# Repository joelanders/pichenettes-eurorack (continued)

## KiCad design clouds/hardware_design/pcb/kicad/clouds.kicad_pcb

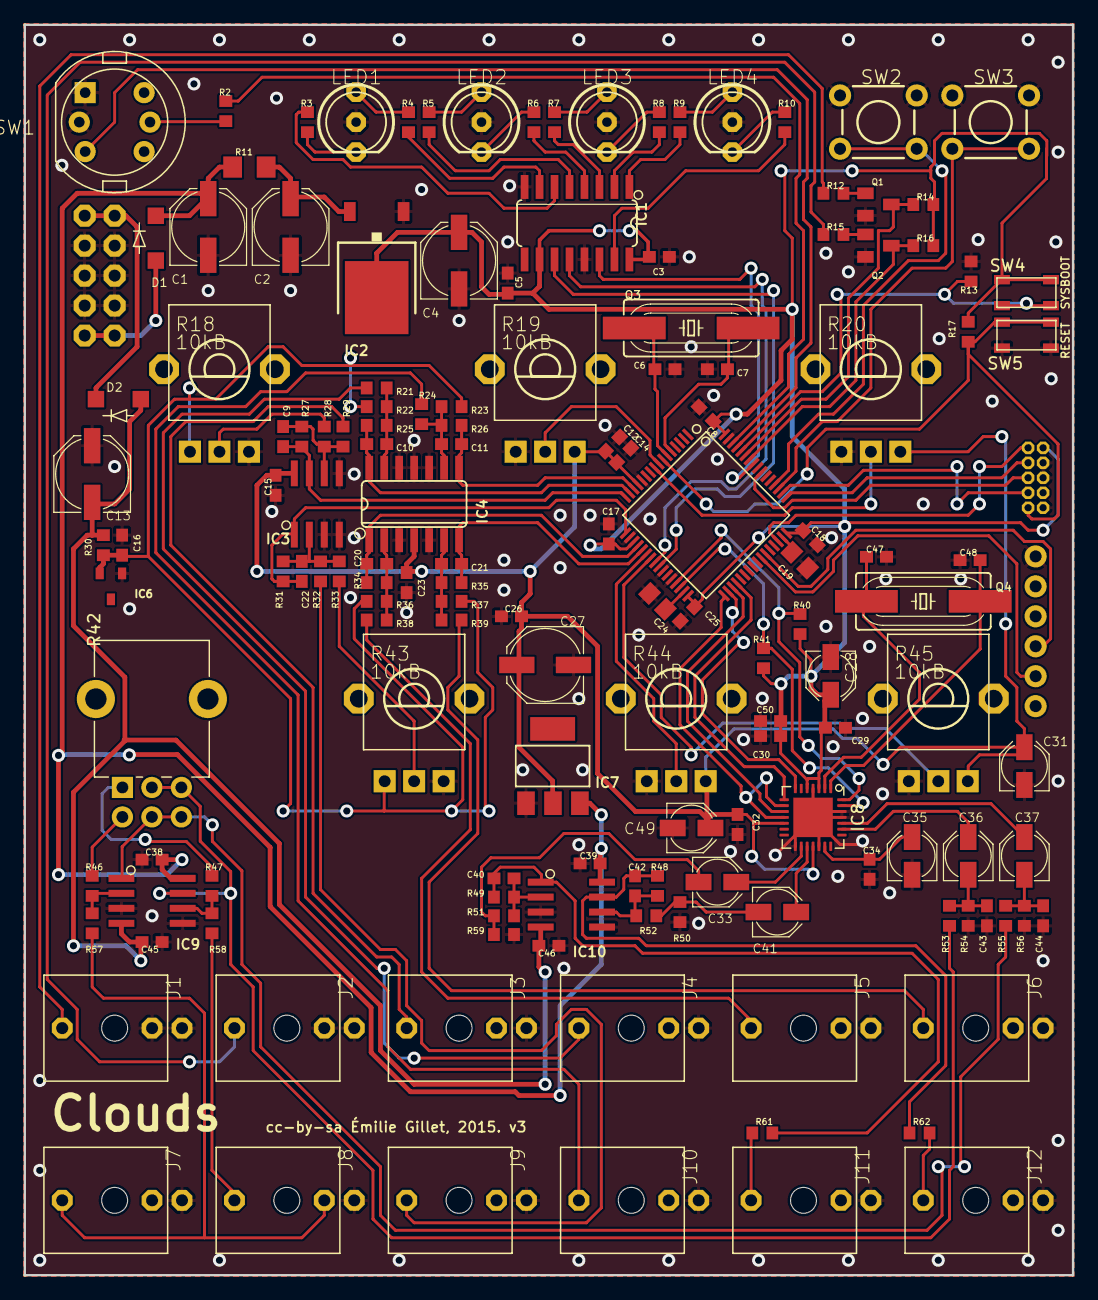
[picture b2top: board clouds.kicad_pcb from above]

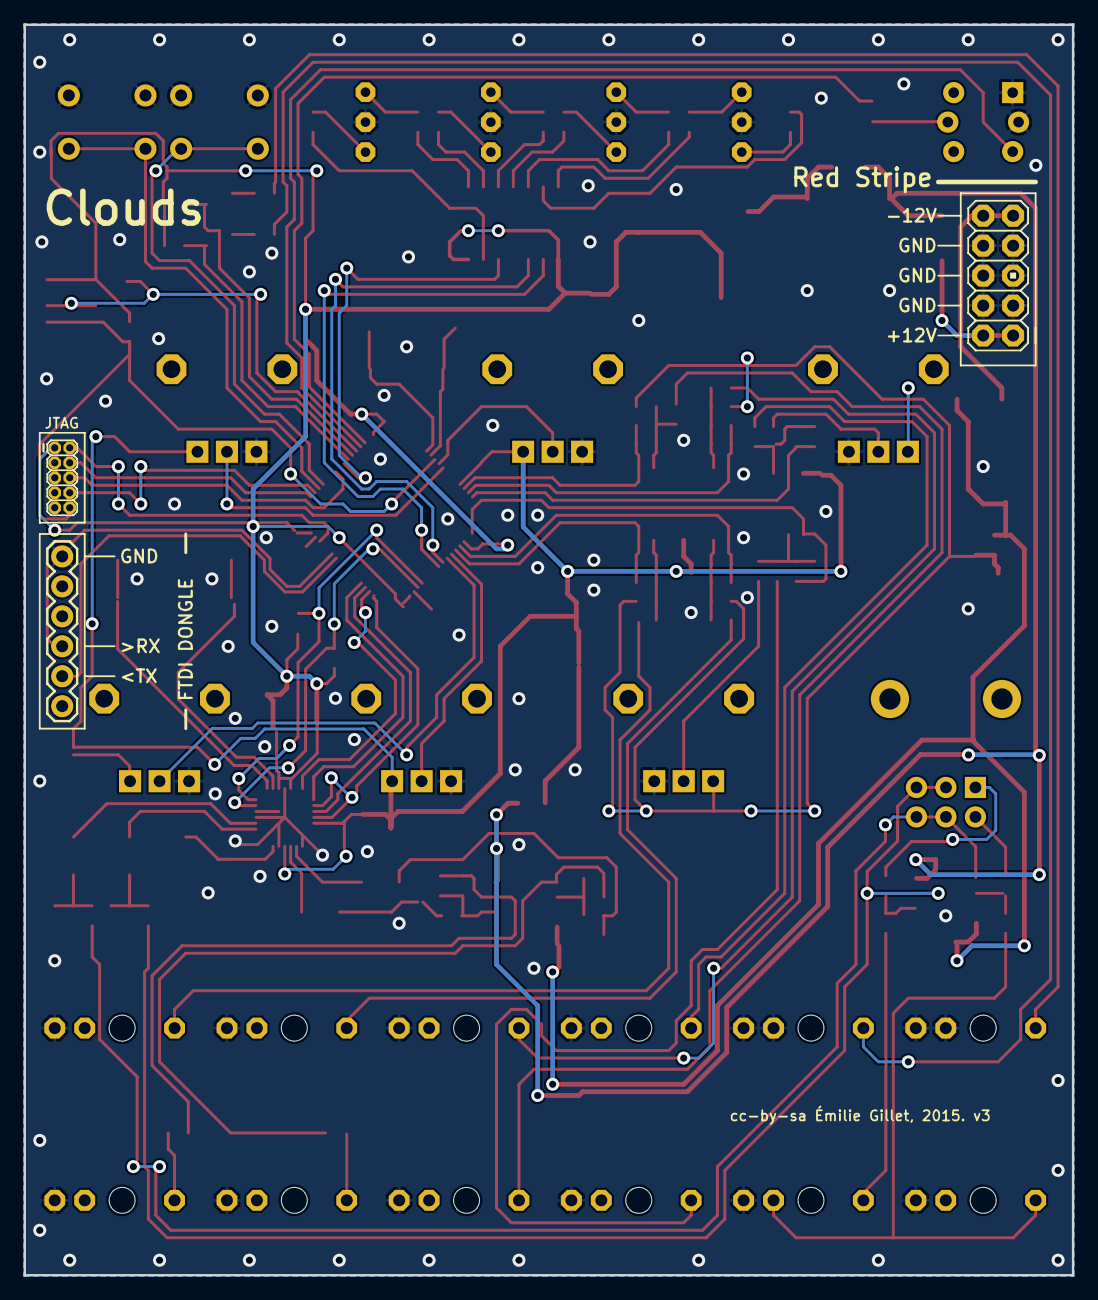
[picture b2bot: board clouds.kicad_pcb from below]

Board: 2 copper layers, 88.9 x 106.0 mm, 150 parts (3 on the bottom side), 106 nets.

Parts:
C1, C2, C4, C13, C27: 47u; PANASONIC_D
C3, C5, C8, C14, C15, C16, C17, C18, C23, C25, C26, C29, C30, C32, C34, C38, C39, C45, C46: 100n; C0603
C6, C7, C40, C42, C47, C48: 18p; C0603
C9, C10, C11, C20, C21, C22: 1n; C0603
C12, C50: 1u; C0603
C19, C24: 2.2u; C0805
C28, C31, C33, C35, C36, C37, C41, C49: 10u; PANASONIC_B
C43, C44: 220p; C0603
D1, D2: 1N5819HW; SOD123
IC1: 74595D; SO16
IC2: LM1117-3.3; TO252
IC3: MCP6002; SO08
IC4: MCP6004; SO14
IC5: STM32F405RGT6; TQFP-10X10-64
IC6: LM4040B10; DBZ_R-PDSO-G3
IC7: LM1117-3.3; SOT223
IC8: WM8731; QFN-28-1EP_5x5mm_P0.5mm_EP3.35x3.35mm
IC9, IC10: TL072D; SO08
J1, J2, J3, J4, J5, J6, J7, J8, J9, J10, J11, J12: PJ301_THONKICONN6; WQP_PJ_301M6
JP1: M06SIP; 1X06
JP2: M05X2MINIJTAG; 2X5-1.27
JP3: M05X2PTH; AVR_ICSP
LED1, LED2, LED3, LED4: WP59EGW; LED-BICOLOR-THROUGHHOLE-5MM
Q1, Q2: MMBT3904; SOT23-BEC
Q3: 8MHz; HC49UP
Q4: 12.288MHz; HC49UP
R2: 1k; R0603
R3, R4, R5, R6, R7, R8, R9, R10: 68; R0603
R11: 4.7; R1206
R12, R15, R21, R24, R29, R32, R38, R39: 100k; R0603
R13, R14, R16, R17: 10k; R0603
R18, R19, R20, R43, R44, R45: 10kB; ALPS_POT_VERTICAL_PS
R22, R23, R28, R33, R37: 200k; R0603
R25, R26, R35: 33k; R0603
R27, R31: 66.5k; R0603
R30: 470; R0603
R34: 47k; R0603
R36: 180k; R0603
R40, R41: 2.2k; R0603
R42: R_Potentiometer_Dual_Separate; Potentiometer_Alpha_RD902F-40-00D_Dual_Vertical_CircularHol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
R46, R47: 3.3k; R0603
R48, R49, R50, R59: 39k; R0603
R51, R52, R53, R54, R55, R56: 5.6k; R0603
R57, R58: 22k; R0603
R61, R62: 1.0k; R0603
SW1: SW_Push_LED; C&K_D6R
SW2, SW3: TAC_SWITCHPTH; TACTILE-PTH
SW4, SW5: EVQQ2; k2-1808 pushbutton switch

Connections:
+3V3: C3.1, C4.+, C5.1, C8.1, C17.1, C18.1, C25.1, C28.+, C29.1, C30.1, C50.1, IC1.10 (SCL), IC1.16 (VCC), IC2.3 (VOUT), IC5.19 (VDD_4), IC5.32 (VDD_1), IC5.48 (VDD_2), IC5.64 (VDD_3), IC8.3 (DCVDD), IC8.5 (DBVDD), JP2.1, R14.2, R16.2, R17.2, R40.2, R41.2, SW4.B (S), SW4.B' (S1)
+3V3_A: C12.1, C14.1, C15.1, C23.1, C26.1, C27.+, C31.+, C32.1, C49.+, IC3.8 (V+), IC4.4 (V+), IC5.13 (VDDA), IC7.2 (VOUT), IC8.12 (HPVDD), IC8.18 (AVDD), R19.P$1 (E), R20.P$1 (E), R44.P$1 (E), R45.P$1 (E)
/clouds_2/BOOT_FLASH: IC5.60 (BOOT0), R13.2, SW4.A, SW4.A' (P1)
/clouds_2/I2C_SCL: IC5.29 (PB10/SPI2_SCK/I2S_SCK/I2C2_SCL/USART3_TX), IC8.28 (SCLK), R40.1
/clouds_2/I2C_SDA: IC5.30 (PB11/I2C2_SDA/USART3_RX), IC8.27 (SDIN), R41.1
/clouds_2/I2S_LRCK: IC5.33 (PB12/SPI2_NSS/I2S2_WS/I2C2_SMBA/USART3_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), IC8.9 (DACLRC), IC8.11 (ADCLRC)
/clouds_2/I2S_SCK: IC5.34 (PB13/SPI2_SCK/I2S2_SCK/USART3_CTS/TIM1_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), IC8.7 (BCLK)
/clouds_2/I2S_SIN: IC5.35 (PB14/SPI2_MISO/USART3_RTS/TIM1_CH2N), IC8.10 (ADCDAT)
/clouds_2/I2S_SOUT: IC5.36 (PB15/SPI2_MOSI/I2S2_SD/TIM1_CH3N), IC8.8 (DACDAT)
/clouds_2/JTCK: IC5.49 (PA14/JTCK-SWCLK), JP2.4
/clouds_2/JTDI: IC5.50 (PA15/JTDI/SPI3_NSS/I2S3_WS), JP2.8
/clouds_2/JTDO: IC5.55 (PB3/JTDO/SPI3_SCK/I2S3_SCK), JP2.6
/clouds_2/JTMS: IC5.46 (PA13/JTMS-SWDAT), JP2.2
/clouds_2/RESET: IC5.7 (NRST), JP2.10, R17.1, SW5.B (S), SW5.B' (S1)
/clouds_2/RX: IC5.43 (PA10/USART1_RX/TIM1_CH3), JP1.4
/clouds_2/TX: IC5.42 (PA9/USART1_TX/TIM1_CH2), JP1.5
AREF_-10: C16.1, IC6.2 (A), R18.P$3 (A), R22.2, R23.2, R30.2, R36.2, R37.2, R43.P$3 (A)
BLEND_CV: C21.2, IC4.7 (OUT), IC5.21 (PA5/SPI1_SCK/ADC5/DAC2), R35.1
BLEND_POT: IC5.23 (PA7/SPI1_MOSI/ADC7/TIM3_CH2), R45.P$2 (S)
DENSITY_CV: C22.2, IC3.1 (OUT), IC5.17 (PA3/USART2_RX/ADC3/TIM2_CH4), R31.1
GND: C1.-, C2.-, C3.2, C4.-, C5.2, C6.1, C7.1, C8.2, C12.2, C13.+, C14.2, C15.2, C16.2, C17.2, C18.2, C19.2, C23.2, C24.2, C25.2, C26.2, C27.-, C28.-, C29.2, C30.2, C31.-, C32.2, C34.2, C35.-, C38.2, C39.2, C43.2, C44.2, C45.1, C46.1, C47.1, C48.1, C49.-, C50.2, IC1.8 (GND), IC1.13 (G), IC2.1 (GND), IC3.3 (+IN), IC3.4 (V-), IC3.5 (+IN), IC4.3 (+IN), IC4.5 (+IN), IC4.10 (+IN), IC4.11 (V-), IC4.12 (+IN), IC5.12 (VSSA), IC5.18 (VSS_4), IC5.26 (PB0/ADC8/TIM3_CH3), IC5.28 (PB2/BOOT1), IC5.63 (VSS_3), IC6.1 (C), IC7.1 (GND), IC8.4 (DGND), IC8.15 (HPGND), IC8.19 (AGND), IC8.25 (MODE), IC8.26 (CSB), IC8.29 (PAD), IC9.3 (+IN), IC9.5 (+IN), IC10.3 (+IN), IC10.5 (+IN), J1.P1 (1), J1.P2 (2), J2.P1 (1), J2.P2 (2), J3.P1 (1), J4.P1 (1), J5.P1 (1), J6.P1 (1), J7.P1 (1), J8.P1 (1), J9.P1 (1), J10.P1 (1), J11.P1 (1), J12.P1 (1), JP1.1, JP2.3, JP2.5, JP2.9, JP3.3, JP3.4, JP3.5, JP3.6, JP3.7, JP3.8, LED1.2 (C), LED2.2 (C), LED3.2 (C), LED4.2 (C), Q1.E, Q2.E, R13.1, R18.P$1 (E), R19.P$3 (A), R20.P$3 (A), R43.P$1 (E), R44.P$3 (A), R45.P$3 (A), R50.1, R54.1, R56.1, R59.1, SW1.1, SW1.2, SW2.1, SW2.2, SW3.1, SW3.2, SW5.A, SW5.A' (P1)
LED_DATA: IC1.14 (SER), IC5.57 (PB5/I2C1_SMBA/SPI1_MOSI/SPI3_MOSI/I2S3_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)
LED_EN: IC1.12 (RCK), IC5.24 (PC4/ADC14)
LED_REC: IC5.62 (PB9/SPI2_NSS/I2S2_WS/I2C1_SDA/TIM4_CH4), R2.1
LED_SCK: IC1.11 (SCK), IC5.25 (PC5/ADC15)
LIN: C37.+, IC8.24 (LLINEIN)
LOUT: C33.+, IC8.16 (LOUT)
unnamed: C2.+, IC2.2 (VIN), R11.2
unnamed: C6.2, IC5.6 (PD1/OSC_OUT), Q3.1
unnamed: C7.2, IC5.5 (PD0/OSC_IN), Q3.2
unnamed: C9.1, IC3.6 (-IN), R27.2, R28.1, R29.1
unnamed: C10.1, IC4.13 (-IN), R21.1, R22.1, R25.2
unnamed: C11.1, IC4.9 (-IN), R23.1, R24.1, R26.2
unnamed: C19.1, IC5.47 (VCAP_2)
unnamed: C20.1, IC4.2 (-IN), R34.2, R36.1, R38.1
unnamed: C21.1, IC4.6 (-IN), R35.2, R37.1, R39.1
unnamed: C22.1, IC3.2 (-IN), R31.2, R32.1, R33.1
unnamed: C24.1, IC5.31 (VCAP_1)
unnamed: C33.-, R51.2, R59.2
unnamed: C34.1, C35.+, IC8.20 (VMID)
unnamed: C36.-, C43.1, R53.1, R54.2
unnamed: C37.-, C44.1, R55.1, R56.2
unnamed: C40.1, IC10.2 (-IN), R49.2, R51.1
unnamed: C40.2, IC10.1 (OUT), R49.1, R61.2
unnamed: C41.-, R50.2, R52.2
unnamed: C42.1, IC10.6 (-IN), R48.2, R52.1
unnamed: C42.2, IC10.7 (OUT), R48.1, R62.2
unnamed: C47.2, IC8.2 (XTO), Q4.1
unnamed: C48.2, IC8.1 (XTI/MCLK), Q4.2
unnamed: D1.A, JP3.1, JP3.2
unnamed: D2.C, JP3.9, JP3.10
unnamed: IC1.1 (QB), R9.2
unnamed: IC1.2 (QC), R8.2
unnamed: IC1.3 (QD), R7.2
unnamed: IC1.4 (QE), R6.2
unnamed: IC1.5 (QF), R5.2
unnamed: IC1.6 (QG), R3.2
unnamed: IC1.7 (QH), R4.2
unnamed: IC1.15 (QA), R10.2
unnamed: IC9.1 (OUT), R42.5, R42.6, R55.2
unnamed: IC9.2 (-IN), R46.2, R57.1
unnamed: IC9.6 (-IN), R47.2, R58.1
unnamed: IC9.7 (OUT), R42.2, R42.3, R53.2
unnamed: J1.P3 (3), R12.1
unnamed: J2.P3 (3), R15.1
unnamed: J3.P3 (3), R29.2
unnamed: J4.P3 (3), R21.2
unnamed: J5.P3 (3), R38.2
unnamed: J6.P3 (3), R39.2
unnamed: J7.P3 (3), J8.P2 (2), R57.2
unnamed: J8.P3 (3), R58.2
unnamed: J9.P3 (3), R32.2
unnamed: J10.P3 (3), R24.2
unnamed: J11.P3 (3), R61.1
unnamed: J12.P3 (3), R62.1
unnamed: LED1.1 (RED), R3.1
unnamed: LED1.3 (GRN), R4.1
unnamed: LED2.1 (RED), R6.1
unnamed: LED2.3 (GRN), R5.1
unnamed: LED3.1 (RED), R8.1
unnamed: LED3.3 (GRN), R7.1
unnamed: LED4.1 (RED), R10.1
unnamed: LED4.3 (GRN), R9.1
unnamed: Q1.B, R12.2
unnamed: Q2.B, R15.2
unnamed: R2.2, SW1.3
unnamed: R18.P$2 (S), R28.2
unnamed: R33.2, R43.P$2 (S)
unnamed: R42.1, R47.1
unnamed: R42.4, R46.1
PITCH_POT: IC5.9 (PC1/ADC11), R20.P$2 (S)
PLAY: IC5.58 (PB6/I2C1_SCL/TIM4_CH1/USART1_TX), Q2.C, R16.1
POSITION_POT_CV: C9.2, IC3.7 (OUT), IC5.16 (PA2/USART2_TX/ADC2/TIM2_CH3), R27.1
REC: IC5.59 (PB7/I2C1_SDA/TIM4_CH2/USART1_RX), Q1.C, R14.1
RIN: C36.+, IC8.23 (RLINEIN)
ROUT: C41.+, IC8.17 (ROUT)
SIZE_CV: C10.2, IC4.14 (OUT), IC5.15 (PA1/USART2_RTS/UART4_RX/ADC1/TIM2_CH2), R25.1
SIZE_POT: IC5.8 (PC0/ADC10), R19.P$2 (S)
SW_LOAD: IC5.51 (PC10/SPI3_SCK/I2S3_SCK/UART4_TX), SW3.3, SW3.4
SW_MODE: IC5.52 (PC11/UART4_RX/SPI3_MISO/USART3_RX), SW2.3, SW2.4
SW_REC: IC5.61 (PB8/TIM4_CH3/I2C1_SCL), SW1.4
TEXTURE_CV: C11.2, IC4.8 (OUT), IC5.14 (PA0-WKUP/USART2_CTS/UART4_TX/ADC0/TIM2_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), R26.1
TEXTURE_POT: IC5.22 (PA6/SPI1_MISO/ADC6/TIM3_CH1), R44.P$2 (S)
VCC: C1.+, C38.1, C39.1, D1.C, IC7.3 (VIN), IC9.8 (V+), IC10.8 (V+), R11.1
VEE: C13.-, C45.2, C46.2, D2.A, IC9.4 (V-), IC10.4 (V-), R30.1
V_OCT: C20.2, IC4.1 (OUT), IC5.20 (PA4/SPI1_NSS/SPI3_NSS/USART2_CK/I2S3_WS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), R34.1

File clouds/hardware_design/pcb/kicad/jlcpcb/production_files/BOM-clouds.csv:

Comment,Designator,Footprint,LCSC
8MHz,Q3,HC49UP,
18p,C6,C0603,
EVQQ2,SW5,k2-1808 pushbutton switch,
10k,R17,R0603,
18p,C7,C0603,
EVQQ2,SW4,k2-1808 pushbutton switch,
10k,R13,R0603,
100n,C18,C0603,
100n,C25,C0603,
100n,C17,C0603,
100n,C14,C0603,
1u,C12,C0603,
100n,C32,C0603,
M05X2MINIJTAG,JP2,2X5-1.27,
100n,C8,C0603,
STM32F405RGT6,IC5,TQFP-10X10-64,
2.2u,C24,C0805,
2.2u,C19,C0805,
100n,C30,C0603,
M06SIP,JP1,1X06,
MCP6004,IC4,SO14,
100k,R21,R0603,
33k,R25,R0603,
200k,R22,R0603,
1n,C10,C0603,
100k,R24,R0603,
33k,R26,R0603,
200k,R23,R0603,
1n,C11,C0603,
100k,R38,R0603,
47k,R34,R0603,
180k,R36,R0603,
1n,C20,C0603,
100k,R39,R0603,
33k,R35,R0603,
1n,C21,C0603,
LM4040B10,IC6,DBZ_R-PDSO-G3,
470,R30,R0603,
100n,C16,C0603,
47u,C1,PANASONIC_D,
47u,C13,PANASONIC_D,
47u,C4,PANASONIC_D,
100n,C3,C0603,
1N5819HW,D1,SOD123,
1N5819HW,D2,SOD123,
M05X2PTH,JP3,AVR_ICSP,
200k,R37,R0603,
100n,C23,C0603,
WM8731,IC8,QFN-28-1EP_5x5mm_P0.5mm_EP3.35x3.35mm,
100n,C29,C0603,
100n,C34,C0603,
10u,C35,PANASONIC_B,
5.6k,R53,R0603,
5.6k,R54,R0603,
220p,C43,C0603,
5.6k,R55,R0603,
5.6k,R56,R0603,
220p,C44,C0603,
10u,C36,PANASONIC_B,
10u,C37,PANASONIC_B,
10u,C41,PANASONIC_B,
39k,R50,R0603,
5.6k,R52,R0603,
TL072D,IC10,SO08,
39k,R48,R0603,
18p,C42,C0603,
1.0k,R62,R0603,
10u,C33,PANASONIC_B,
39k,R59,R0603,
5.6k,R51,R0603,
39k,R49,R0603,
18p,C40,C0603,
1.0k,R61,R0603,
100n,C39,C0603,
100n,C46,C0603,
2.2k,R40,R0603,
2.2k,R41,R0603,
10kB,R43,ALPS_POT_VERTICAL_PS,
100k,R32,R0603,
66.5k,R31,R0603,
200k,R33,R0603,
1n,C22,C0603,
100k,R29,R0603,
66.5k,R27,R0603,
1n,C9,C0603,
10kB,R18,ALPS_POT_VERTICAL_PS,
200k,R28,R0603,
MCP6002,IC3,SO08,
SW_Push_LED,SW1,C&K_D6R,
MMBT3904,Q1,SOT23-BEC,
100k,R12,R0603,
MMBT3904,Q2,SOT23-BEC,
100k,R15,R0603,
10k,R16,R0603,
10k,R14,R0603,
1k,R2,R0603,
100n,C15,C0603,
10kB,R19,ALPS_POT_VERTICAL_PS,
10kB,R44,ALPS_POT_VERTICAL_PS,
10kB,R20,ALPS_POT_VERTICAL_PS,
10kB,R45,ALPS_POT_VERTICAL_PS,
TAC_SWITCHPTH,SW2,TACTILE-PTH,
TAC_SWITCHPTH,SW3,TACTILE-PTH,
WP59EGW,LED4,LED-BICOLOR-THROUGHHOLE-5MM,
WP59EGW,LED3,LED-BICOLOR-THROUGHHOLE-5MM,
WP59EGW,LED2,LED-BICOLOR-THROUGHHOLE-5MM,
WP59EGW,LED1,LED-BICOLOR-THROUGHHOLE-5MM,
74595D,IC1,SO16,
68,R10,R0603,
68,R9,R0603,
68,R8,R0603,
68,R7,R0603,
68,R6,R0603,
68,R5,R0603,
68,R3,R0603,
68,R4,R0603,
R_Potentiometer_Dual_Separate,R42,Potentiometer_Alpha_RD902F-40-00D_Dual_Vertical_CircularHoles,
3.3k,R47,R0603,
3.3k,R46,R0603,
TL072D,IC9,SO08,
22k,R58,R0603,
22k,R57,R0603,
100n,C38,C0603,
100n,C45,C0603,
100n,C5,C0603,
47u,C27,PANASONIC_D,
100n,C26,C0603,
LM1117-3.3,IC7,SOT223,
PJ301_THONKICONN6,J8,WQP_PJ_301M6,
PJ301_THONKICONN6,J12,WQP_PJ_301M6,
PJ301_THONKICONN6,J7,WQP_PJ_301M6,
PJ301_THONKICONN6,J11,WQP_PJ_301M6,
PJ301_THONKICONN6,J3,WQP_PJ_301M6,
PJ301_THONKICONN6,J5,WQP_PJ_301M6,
PJ301_THONKICONN6,J6,WQP_PJ_301M6,
PJ301_THONKICONN6,J9,WQP_PJ_301M6,
PJ301_THONKICONN6,J4,WQP_PJ_301M6,
PJ301_THONKICONN6,J10,WQP_PJ_301M6,
PJ301_THONKICONN6,J1,WQP_PJ_301M6,
PJ301_THONKICONN6,J2,WQP_PJ_301M6,
LM1117-3.3,IC2,TO252,
47u,C2,PANASONIC_D,
4.7,R11,R1206,
12.288MHz,Q4,HC49UP,
18p,C47,C0603,
18p,C48,C0603,
10u,C49,PANASONIC_B,
10u,C28,PANASONIC_B,
10u,C31,PANASONIC_B,
1u,C50,C0603,

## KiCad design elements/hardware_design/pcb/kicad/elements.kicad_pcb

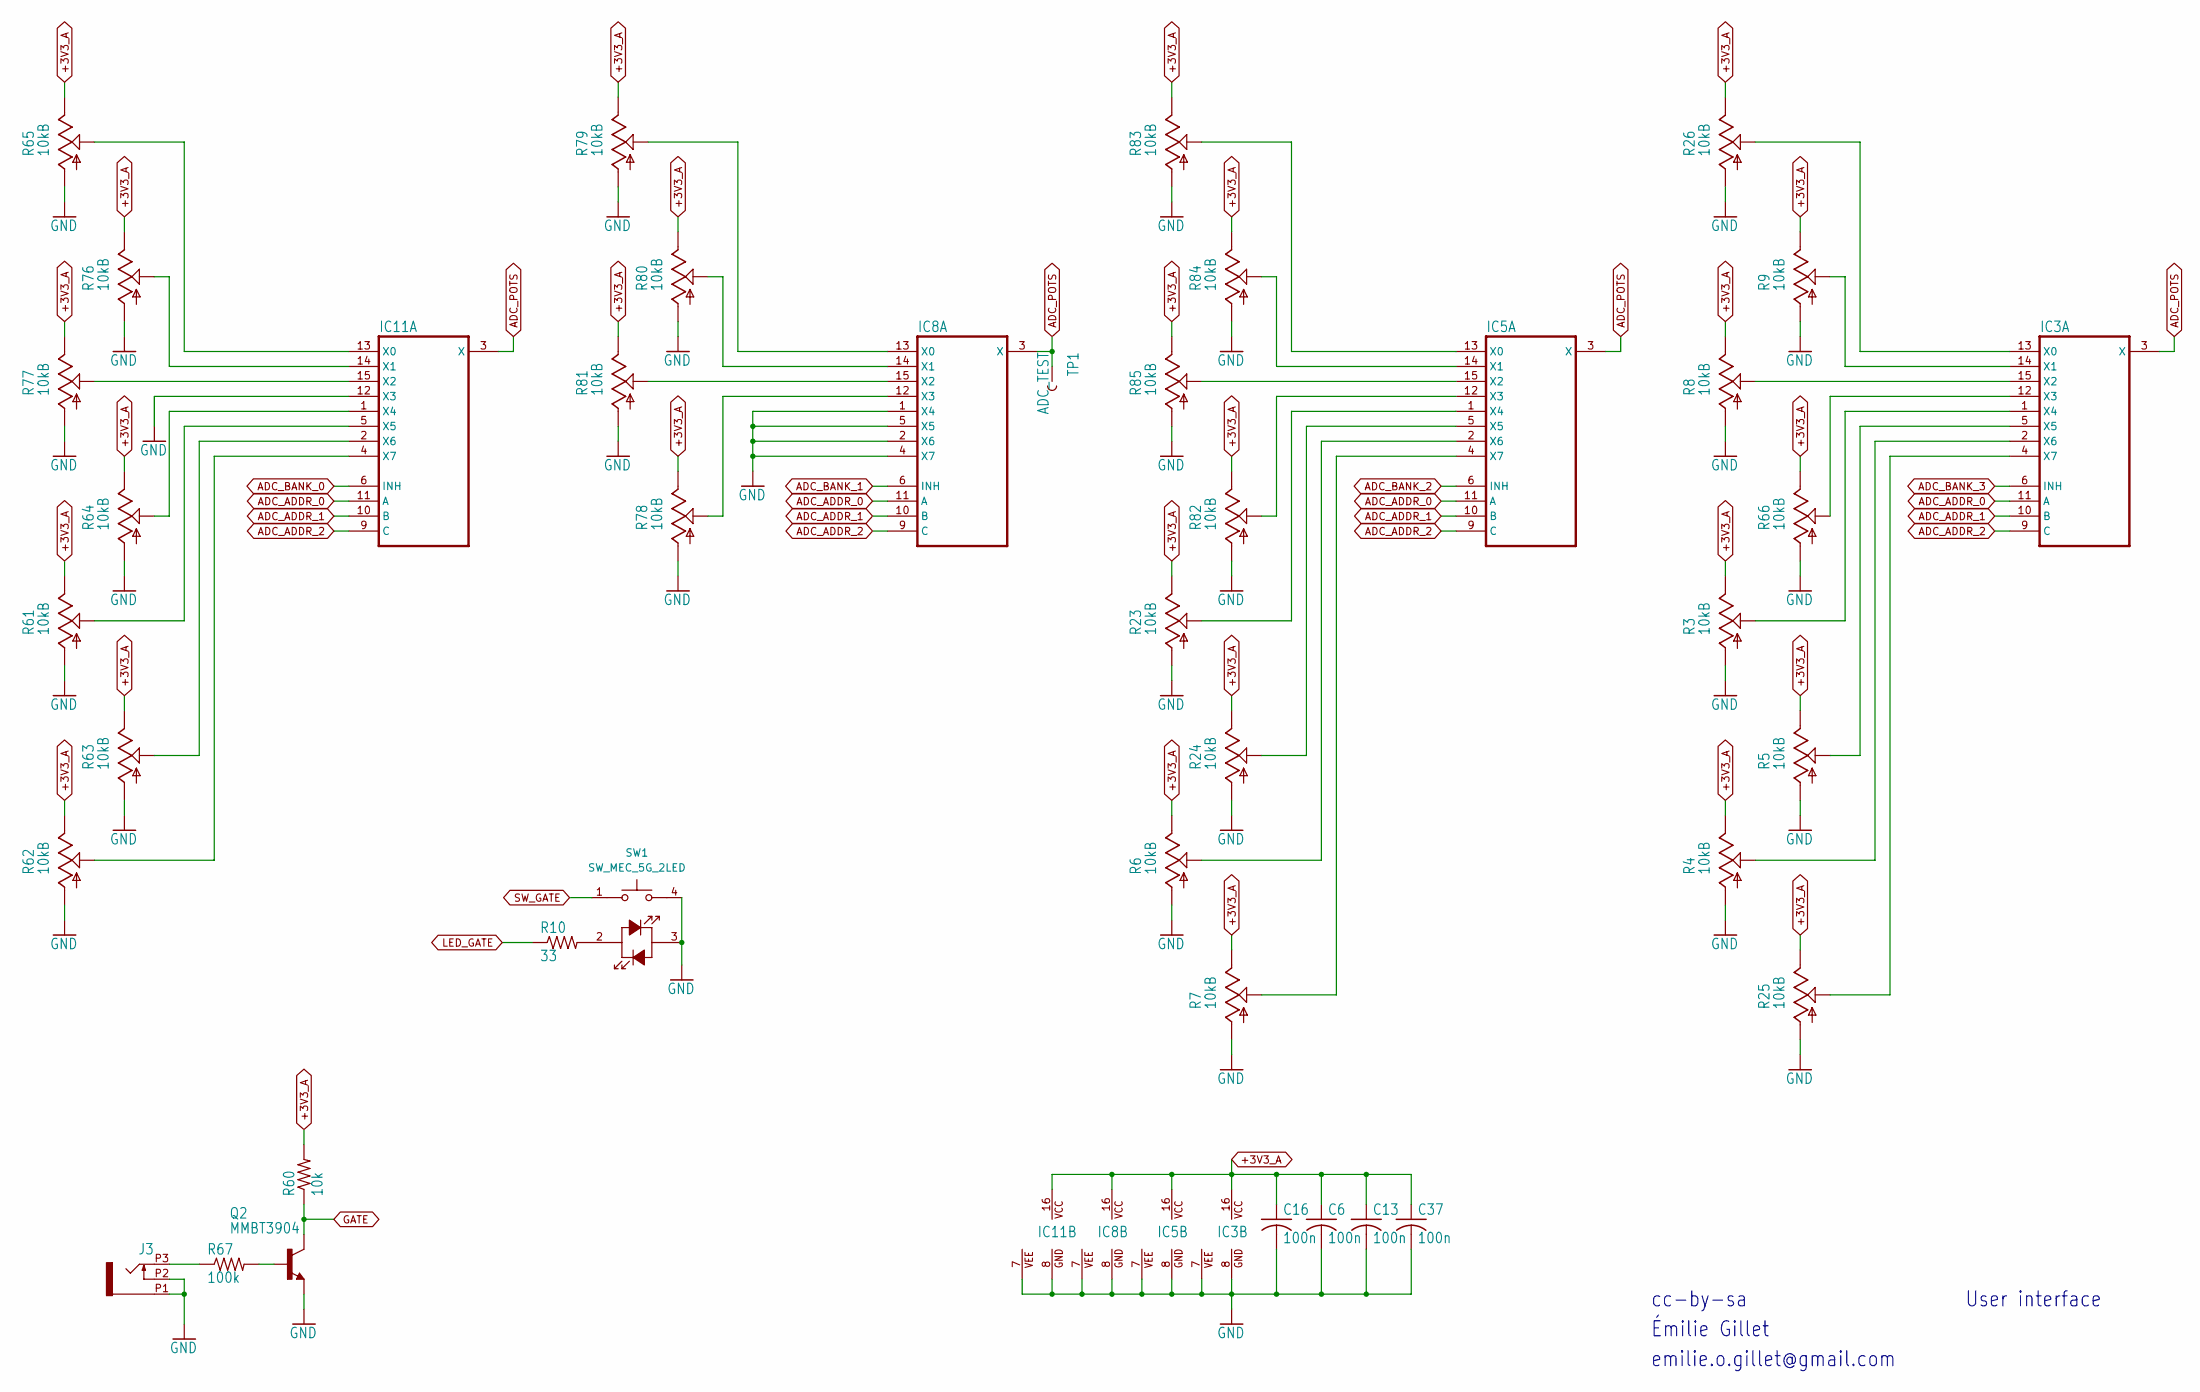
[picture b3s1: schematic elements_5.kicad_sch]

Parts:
C6, C13, C16, C37: 100n; C0603
IC3, IC5, IC8, IC11: 4051PW; TSSOP16
J3: PJ301_THONKICONN6; WQP_PJ_301M6
Q2: MMBT3904; SOT23-BEC
R3, R4, R5, R6, R7, R8, R9, R23, R24, R25, R26, R61, R62, R63, R64, R65, R66: 10kB; ALPS_POT_VERTICAL_PS
R10: 33; R0603
R60: 10k; R0603
R67: 100k; R0603
R76, R77, R78, R79, R80, R81, R82, R83, R84, R85: 10kB; ALPS_POT_VERTICAL
SW1: SW_MEC_5G_2LED; C&K_D6R
TP1: ADC_TEST; PAD.03X.03

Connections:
+3V3_A: C6.1, C13.1, C16.1, C37.1, IC3.16 (VCC), IC5.16 (VCC), IC8.16 (VCC), IC11.16 (VCC), R3.P$1 (E), R4.P$1 (E), R5.P$1 (E), R6.P$1 (E), R7.P$1 (E), R8.P$1 (E), R9.P$1 (E), R23.P$1 (E), R24.P$1 (E), R25.P$1 (E), R26.P$1 (E), R60.2, R61.P$1 (E), R62.P$1 (E), R63.P$1 (E), R64.P$1 (E), R65.P$1 (E), R66.P$1 (E), R76.P$1 (E), R77.P$1 (E), R78.P$1 (E), R79.P$1 (E), R80.P$1 (E), R81.P$1 (E), R82.P$1 (E), R83.P$1 (E), R84.P$1 (E), R85.P$1 (E); also elsewhere on the board
ADC_ADDR_0: IC3.11 (A), IC5.11 (A), IC8.11 (A), IC11.11 (A); also elsewhere on the board
ADC_ADDR_1: IC3.10 (B), IC5.10 (B), IC8.10 (B), IC11.10 (B); also elsewhere on the board
ADC_ADDR_2: IC3.9 (C), IC5.9 (C), IC8.9 (C), IC11.9 (C); also elsewhere on the board
ADC_BANK_0: IC11.6 (INH); also elsewhere on the board
ADC_BANK_1: IC8.6 (INH); also elsewhere on the board
ADC_BANK_2: IC5.6 (INH); also elsewhere on the board
ADC_BANK_3: IC3.6 (INH); also elsewhere on the board
ADC_POTS: IC3.3 (X), IC5.3 (X), IC8.3 (X), IC11.3 (X), TP1.P$1 (1); also elsewhere on the board
GATE: Q2.C, R60.1; also elsewhere on the board
GND: C6.2, C13.2, C16.2, C37.2, IC3.7 (VEE), IC3.8 (GND), IC5.7 (VEE), IC5.8 (GND), IC8.1 (X4), IC8.2 (X6), IC8.4 (X7), IC8.5 (X5), IC8.7 (VEE), IC8.8 (GND), IC11.7 (VEE), IC11.8 (GND), IC11.12 (X3), J3.P1 (1), J3.P2 (2), Q2.E, R3.P$3 (A), R4.P$3 (A), R5.P$3 (A), R6.P$3 (A), R7.P$3 (A), R8.P$3 (A), R9.P$3 (A), R23.P$3 (A), R24.P$3 (A), R25.P$3 (A), R26.P$3 (A), R61.P$3 (A), R62.P$3 (A), R63.P$3 (A), R64.P$3 (A), R65.P$3 (A), R66.P$3 (A), R76.P$3 (A), R77.P$3 (A), R78.P$3 (A), R79.P$3 (A), R80.P$3 (A), R81.P$3 (A), R82.P$3 (A), R83.P$3 (A), R84.P$3 (A), R85.P$3 (A), SW1.3 (K), SW1.4 (A); also elsewhere on the board
LED_GATE: R10.1; also elsewhere on the board
unnamed: IC3.1 (X4), R3.P$2 (S)
unnamed: IC3.2 (X6), R4.P$2 (S)
unnamed: IC3.4 (X7), R25.P$2 (S)
unnamed: IC3.5 (X5), R5.P$2 (S)
unnamed: IC3.12 (X3), R66.P$2 (S)
unnamed: IC3.13 (X0), R26.P$2 (S)
unnamed: IC3.14 (X1), R9.P$2 (S)
unnamed: IC3.15 (X2), R8.P$2 (S)
unnamed: IC5.1 (X4), R23.P$2 (S)
unnamed: IC5.2 (X6), R6.P$2 (S)
unnamed: IC5.4 (X7), R7.P$2 (S)
unnamed: IC5.5 (X5), R24.P$2 (S)
unnamed: IC5.12 (X3), R82.P$2 (S)
unnamed: IC5.13 (X0), R83.P$2 (S)
unnamed: IC5.14 (X1), R84.P$2 (S)
unnamed: IC5.15 (X2), R85.P$2 (S)
unnamed: IC8.12 (X3), R78.P$2 (S)
unnamed: IC8.13 (X0), R79.P$2 (S)
unnamed: IC8.14 (X1), R80.P$2 (S)
unnamed: IC8.15 (X2), R81.P$2 (S)
unnamed: IC11.1 (X4), R64.P$2 (S)
unnamed: IC11.2 (X6), R63.P$2 (S)
unnamed: IC11.4 (X7), R62.P$2 (S)
unnamed: IC11.5 (X5), R61.P$2 (S)
unnamed: IC11.13 (X0), R65.P$2 (S)
unnamed: IC11.14 (X1), R76.P$2 (S)
unnamed: IC11.15 (X2), R77.P$2 (S)
unnamed: J3.P3 (3), R67.1
unnamed: Q2.B, R67.2
unnamed: R10.2, SW1.2
SW_GATE: SW1.1; also elsewhere on the board

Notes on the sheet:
User interface
emilie.o.gillet@gmail.com
cc-by-sa
Émilie Gillet

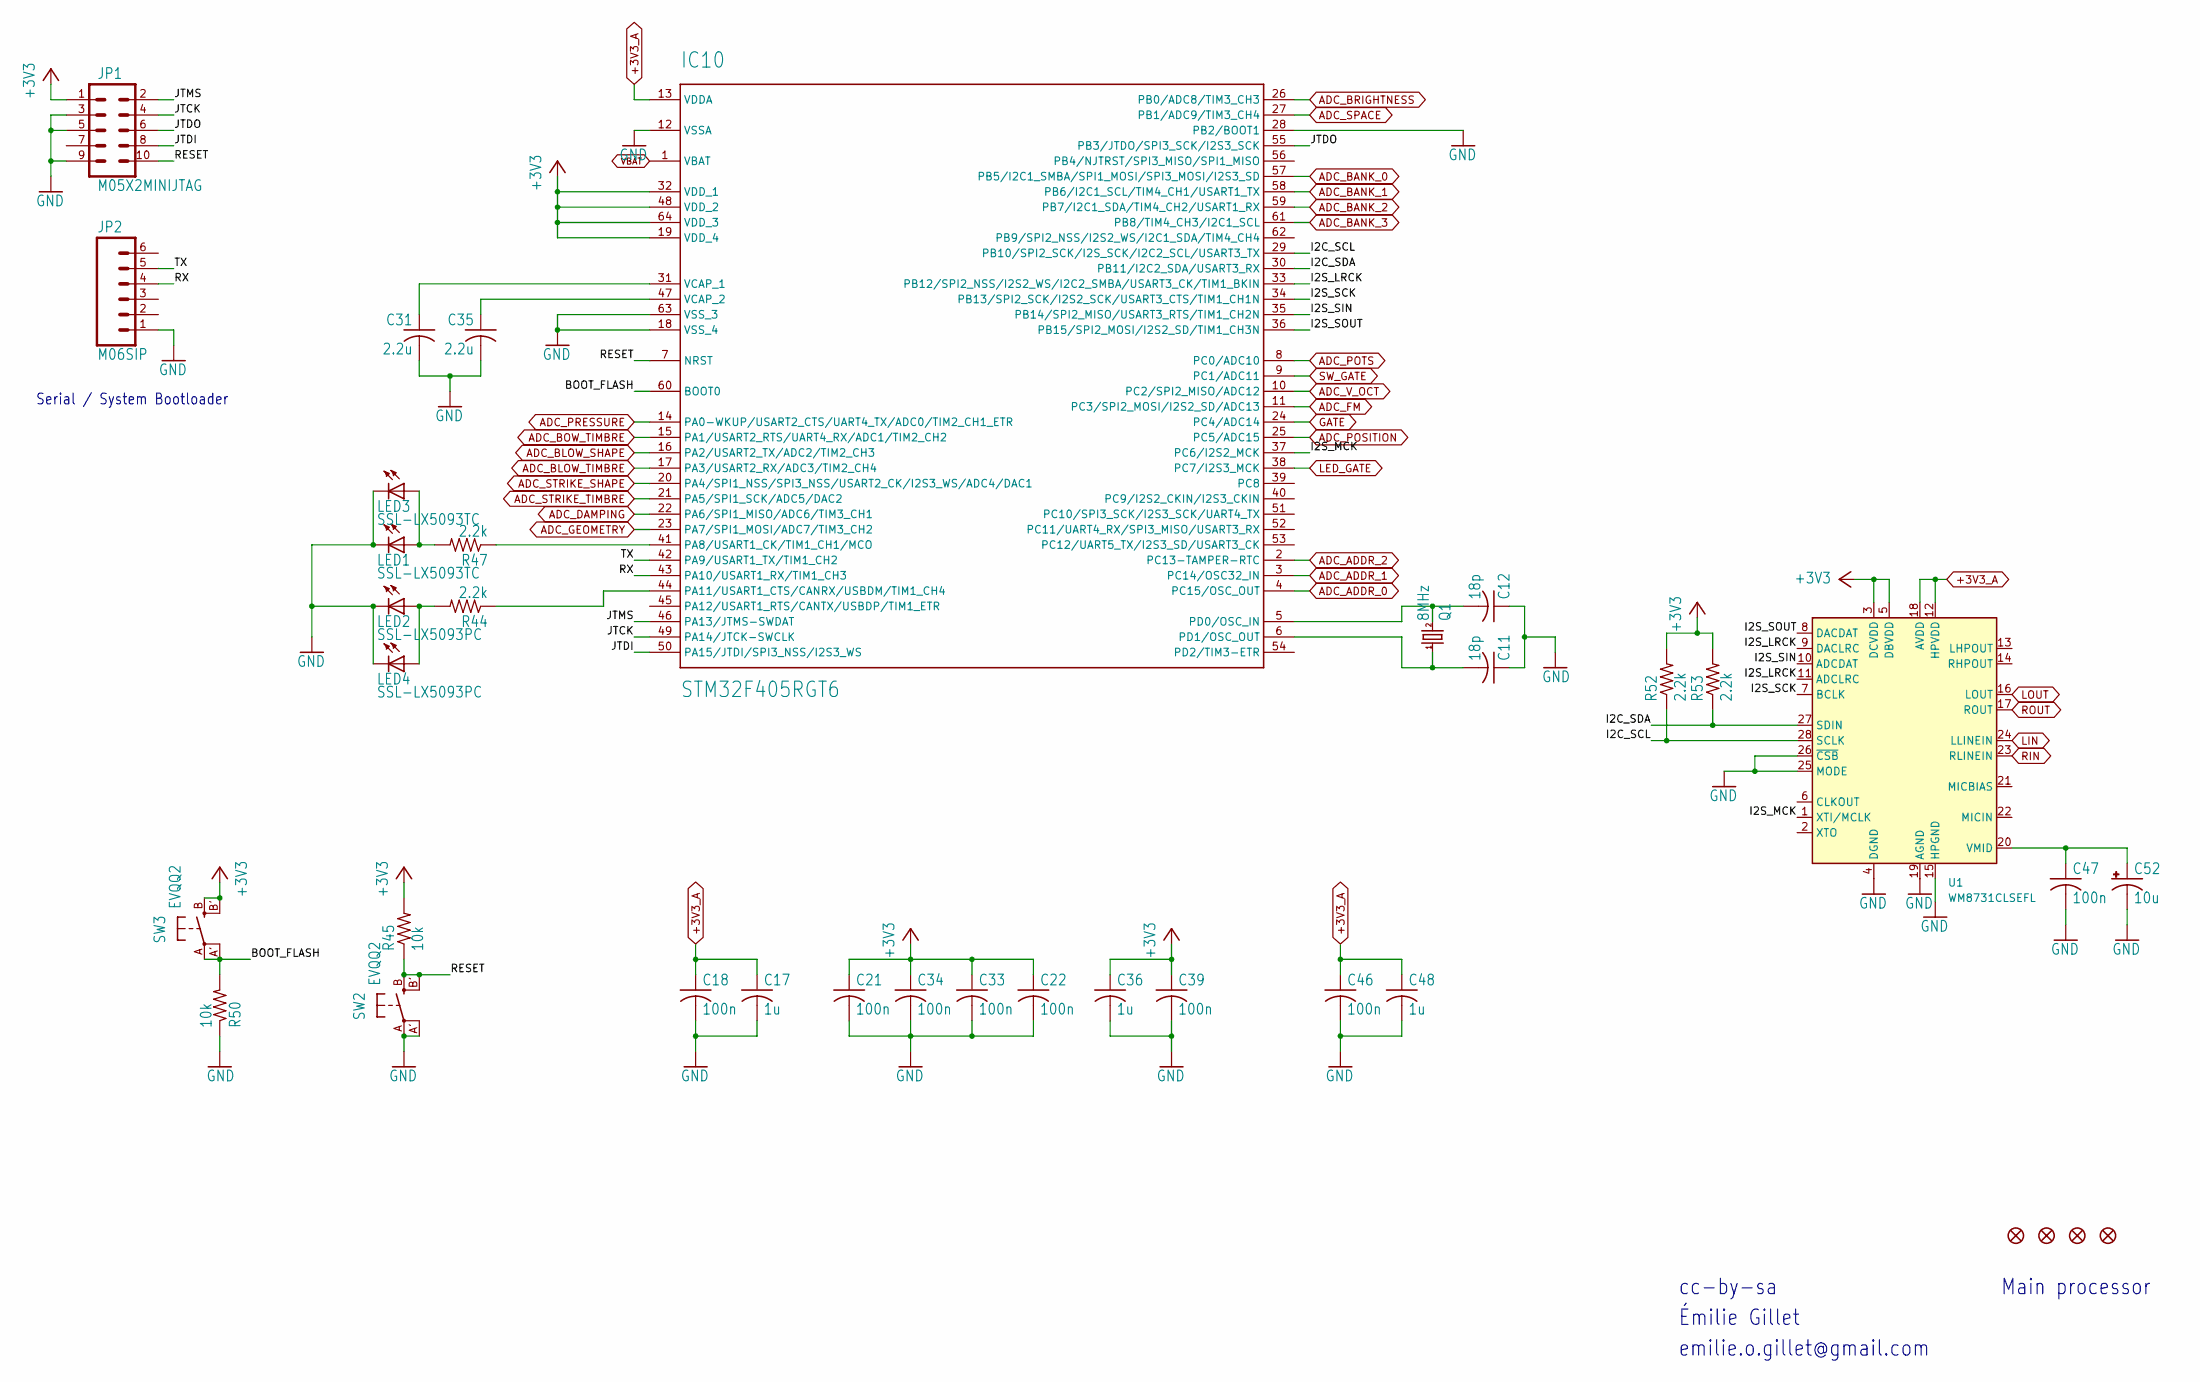
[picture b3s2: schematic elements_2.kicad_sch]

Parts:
C11, C12: 18p; C0603
C17, C36, C48: 1u; C0603
C18, C21, C22, C33, C34, C39, C46, C47: 100n; C0603
C31, C35: 2.2u; C0805
C52: 10u; PANASONIC_B
F1, F2, F3, F4: FIDUCIAL1X2; FIDUCIAL-1X2
IC10: STM32F405RGT6; TQFP-10X10-64
JP1: M05X2MINIJTAG; 2X5-1.27
JP2: M06SIP; 1X06
LED1: SSL-LX5093TC; LED5MM
LED2: SSL-LX5093PC; LED5MM
LED3: SSL-LX5093TC; LED_0603_1608Metric
LED4: SSL-LX5093PC; LED_0603_1608Metric
Q1: 8MHz; HC49UP
R44, R47, R52, R53: 2.2k; R0603
R45, R50: 10k; R0603
SW2, SW3: EVQQ2; k2-1808 pushbutton switch
U1: WM8731CLSEFL; QFN-28-1EP_5x5mm_P0.5mm_EP3.35x3.35mm

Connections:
+3V3: C21.1, C22.1, C33.1, C34.1, C36.1, C39.1, IC10.19 (VDD_4), IC10.32 (VDD_1), IC10.48 (VDD_2), IC10.64 (VDD_3), JP1.1, R45.2, R52.2, R53.2, SW3.B (S), SW3.B' (S1), U1.3 (DCVDD), U1.5 (DBVDD); also elsewhere on the board
+3V3_A: C17.1, C18.1, C46.1, C48.1, IC10.13 (VDDA), U1.12 (HPVDD), U1.18 (AVDD); also elsewhere on the board
/elements_2/BOOT_FLASH: IC10.60 (BOOT0), R50.2, SW3.A, SW3.A' (P1)
/elements_2/I2C_SCL: IC10.29 (PB10/SPI2_SCK/I2S_SCK/I2C2_SCL/USART3_TX), R52.1, U1.28 (SCLK)
/elements_2/I2C_SDA: IC10.30 (PB11/I2C2_SDA/USART3_RX), R53.1, U1.27 (SDIN)
/elements_2/I2S_LRCK: IC10.33 (PB12/SPI2_NSS/I2S2_WS/I2C2_SMBA/USART3_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), U1.9 (DACLRC), U1.11 (ADCLRC)
/elements_2/I2S_MCK: IC10.37 (PC6/I2S2_MCK), U1.1 (XTI/MCLK)
/elements_2/I2S_SCK: IC10.34 (PB13/SPI2_SCK/I2S2_SCK/USART3_CTS/TIM1_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), U1.7 (BCLK)
/elements_2/I2S_SIN: IC10.35 (PB14/SPI2_MISO/USART3_RTS/TIM1_CH2N), U1.10 (ADCDAT)
/elements_2/I2S_SOUT: IC10.36 (PB15/SPI2_MOSI/I2S2_SD/TIM1_CH3N), U1.8 (DACDAT)
/elements_2/JTCK: IC10.49 (PA14/JTCK-SWCLK), JP1.4
/elements_2/JTDI: IC10.50 (PA15/JTDI/SPI3_NSS/I2S3_WS), JP1.8
/elements_2/JTDO: IC10.55 (PB3/JTDO/SPI3_SCK/I2S3_SCK), JP1.6
/elements_2/JTMS: IC10.46 (PA13/JTMS-SWDAT), JP1.2
/elements_2/RESET: IC10.7 (NRST), JP1.10, R45.1, SW2.B (S), SW2.B' (S1)
/elements_2/RX: IC10.43 (PA10/USART1_RX/TIM1_CH3), JP2.4
/elements_2/TX: IC10.42 (PA9/USART1_TX/TIM1_CH2), JP2.5
ADC_ADDR_0: IC10.4 (PC15/OSC_OUT); also elsewhere on the board
ADC_ADDR_1: IC10.3 (PC14/OSC32_IN); also elsewhere on the board
ADC_ADDR_2: IC10.2 (PC13-TAMPER-RTC); also elsewhere on the board
ADC_BANK_0: IC10.57 (PB5/I2C1_SMBA/SPI1_MOSI/SPI3_MOSI/I2S3_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); also elsewhere on the board
ADC_BANK_1: IC10.58 (PB6/I2C1_SCL/TIM4_CH1/USART1_TX); also elsewhere on the board
ADC_BANK_2: IC10.59 (PB7/I2C1_SDA/TIM4_CH2/USART1_RX); also elsewhere on the board
ADC_BANK_3: IC10.61 (PB8/TIM4_CH3/I2C1_SCL); also elsewhere on the board
ADC_BLOW_SHAPE: IC10.16 (PA2/USART2_TX/ADC2/TIM2_CH3); also elsewhere on the board
ADC_BLOW_TIMBRE: IC10.17 (PA3/USART2_RX/ADC3/TIM2_CH4); also elsewhere on the board
ADC_BOW_TIMBRE: IC10.15 (PA1/USART2_RTS/UART4_RX/ADC1/TIM2_CH2); also elsewhere on the board
ADC_BRIGHTNESS: IC10.26 (PB0/ADC8/TIM3_CH3); also elsewhere on the board
ADC_DAMPING: IC10.22 (PA6/SPI1_MISO/ADC6/TIM3_CH1); also elsewhere on the board
ADC_FM: IC10.11 (PC3/SPI2_MOSI/I2S2_SD/ADC13); also elsewhere on the board
ADC_GEOMETRY: IC10.23 (PA7/SPI1_MOSI/ADC7/TIM3_CH2); also elsewhere on the board
ADC_POSITION: IC10.25 (PC5/ADC15); also elsewhere on the board
ADC_POTS: IC10.8 (PC0/ADC10); also elsewhere on the board
ADC_PRESSURE: IC10.14 (PA0-WKUP/USART2_CTS/UART4_TX/ADC0/TIM2_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); also elsewhere on the board
ADC_SPACE: IC10.27 (PB1/ADC9/TIM3_CH4); also elsewhere on the board
ADC_STRIKE_SHAPE: IC10.20 (PA4/SPI1_NSS/SPI3_NSS/USART2_CK/I2S3_WS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); also elsewhere on the board
ADC_STRIKE_TIMBRE: IC10.21 (PA5/SPI1_SCK/ADC5/DAC2); also elsewhere on the board
ADC_V_OCT: IC10.10 (PC2/SPI2_MISO/ADC12); also elsewhere on the board
GATE: IC10.24 (PC4/ADC14); also elsewhere on the board
GND: C11.1, C12.1, C17.2, C18.2, C21.2, C22.2, C31.2, C33.2, C34.2, C35.2, C36.2, C39.2, C46.2, C47.2, C48.2, C52.-, IC10.12 (VSSA), IC10.18 (VSS_4), IC10.28 (PB2/BOOT1), IC10.63 (VSS_3), JP1.3, JP1.5, JP1.9, JP2.1, LED1.K (C), LED2.K (C), LED3.K (C), LED4.K (C), R50.1, SW2.A, SW2.A' (P1), U1.4 (DGND), U1.15 (HPGND), U1.19 (AGND), U1.25 (MODE), U1.26 (~CSB), U1.29 (AGND); also elsewhere on the board
LED_GATE: IC10.38 (PC7/I2S3_MCK); also elsewhere on the board
LIN: U1.24 (LLINEIN); also elsewhere on the board
LOUT: U1.16 (LOUT); also elsewhere on the board
unnamed: C11.2, IC10.6 (PD1/OSC_OUT), Q1.1
unnamed: C12.2, IC10.5 (PD0/OSC_IN), Q1.2
unnamed: C31.1, IC10.31 (VCAP_1)
unnamed: C35.1, IC10.47 (VCAP_2)
unnamed: C47.1, C52.+, U1.20 (VMID)
unnamed: IC10.41 (PA8/USART1_CK/TIM1_CH1/MCO), R47.1
unnamed: IC10.44 (PA11/USART1_CTS/CANRX/USBDM/TIM1_CH4), R44.1
unnamed: LED1.A, LED3.A, R47.2
unnamed: LED2.A, LED4.A, R44.2
RIN: U1.23 (RLINEIN); also elsewhere on the board
ROUT: U1.17 (ROUT); also elsewhere on the board
SW_GATE: IC10.9 (PC1/ADC11); also elsewhere on the board
VBAT: IC10.1 (VBAT)

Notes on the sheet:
Main processor
emilie.o.gillet@gmail.com
Émilie Gillet
Serial / System Bootloader
cc-by-sa
